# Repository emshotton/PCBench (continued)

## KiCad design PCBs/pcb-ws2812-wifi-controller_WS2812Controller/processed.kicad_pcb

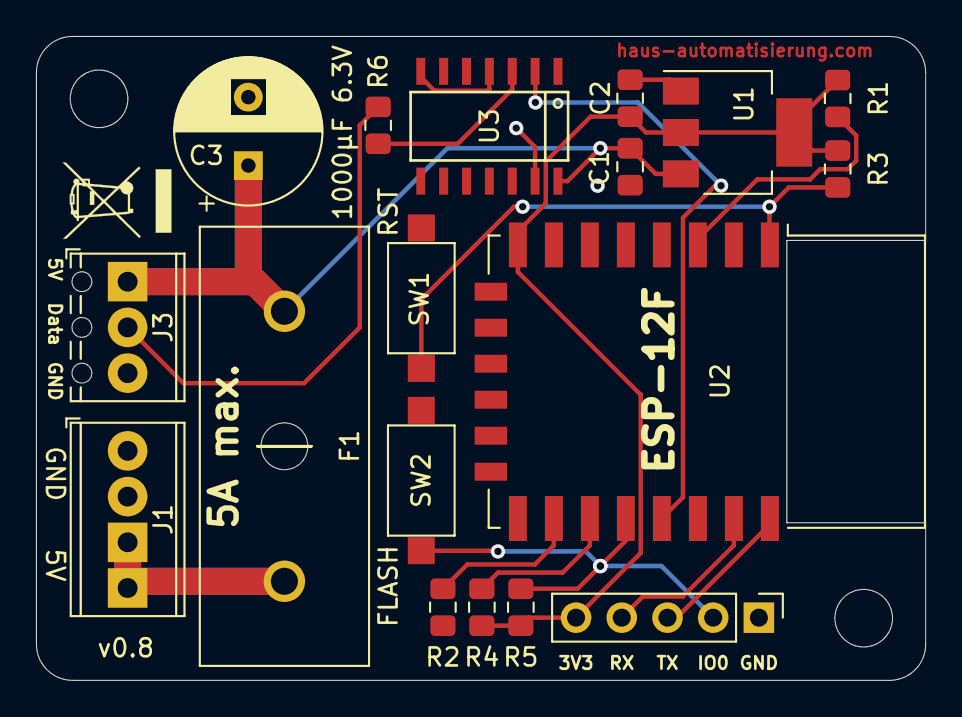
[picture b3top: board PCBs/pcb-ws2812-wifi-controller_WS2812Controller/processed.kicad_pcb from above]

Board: 2 copper layers, 49.4 x 35.8 mm, 18 parts (0 on the bottom side), 14 nets.

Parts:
C1, C2: 100nF; C_0805_2012Metric_Pad1.15x1.40mm_HandSolder
C3: 1000µF; CP_Radial_D8.0mm_P3.80mm
F1: Fuse; Fuse-PTF75_Stelvio
J1: Conn_01x04_Male; TerminalBlock_Phoenix_MPT-0,5-4-2.54_1x04_P2.54mm_Horizontal
J2: Conn_01x05_Male; PinHeader_1x05_P2.54mm_Vertical
J3: Conn_01x03; TerminalBlock_Phoenix_MPT-0,5-3-2.54_1x03_P2.54mm_Horizontal
R1, R2, R3, R4, R5: 10kΩ; R_0805_2012Metric_Pad1.15x1.40mm_HandSolder
R6: 330Ω; R_0805_2012Metric_Pad1.15x1.40mm_HandSolder
SW1: SW_Reset; SW_SPST_CK_RS282G05A3
SW2: SW_GPIO0; SW_SPST_CK_RS282G05A3
U1: AMS1117-3.3; SOT-223-3_TabPin2
U2: ESP-12F; ESP-12E
U3: SN74AHCT125; SN74AHCT125D

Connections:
+3V3: C2.1, J2.5, R1.1, R3.1, R4.1, R5.1, U1.2 (VO), U2.8 (VCC)
+5V: C1.1, C3.1, F1.1, J3.1, U1.3 (VI), U3.14 (VCC)
/EN: R1.2, U2.3 (EN)
/RST: R3.2, SW1.2, U2.1 (~RST)
/SUPPLY: F1.2, J1.3, J1.4
DATA: R6.2, U3.3 (1Y)
GND: C1.2, C2.2, C3.2, J1.1, J1.2, J2.1, J3.3, R2.2, SW1.1, SW2.2, U1.1 (GND), U2.15 (GND), U3.1 (1OE), U3.4 (2OE), U3.7 (GND), U3.10 (3OE), U3.13 (4OE)
GPIO0: J2.2, R5.2, SW2.1, U2.18 (GPIO0)
GPIO4: U2.19 (GPIO4), U3.2 (1A)
unnamed: J3.2, R6.1
unnamed: R2.1, U2.16 (GPIO15)
unnamed: R4.2, U2.17 (GPIO2)
RX: J2.4, U2.21 (GPIO3/RXD)
TX: J2.3, U2.22 (GPIO1/TXD)

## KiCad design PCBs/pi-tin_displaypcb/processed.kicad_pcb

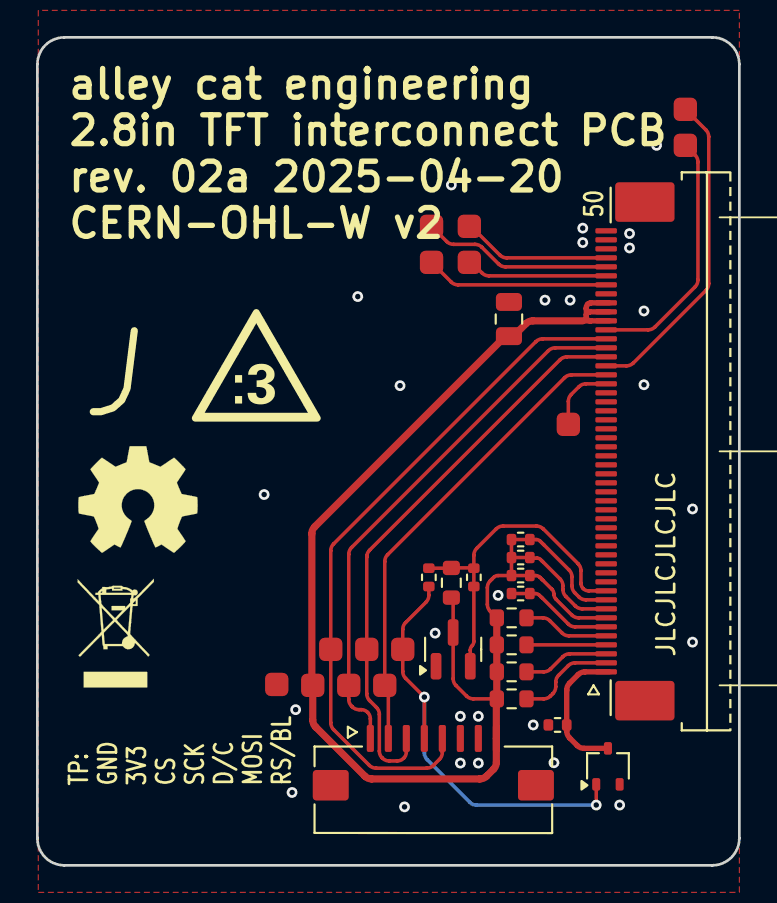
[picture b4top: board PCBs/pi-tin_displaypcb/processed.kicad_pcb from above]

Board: 2 copper layers, 39.0 x 46.0 mm, 32 parts (1 on the bottom side), 25 nets.

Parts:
C101: 10u; C_0805_2012Metric
J102: FPC09-Q1.0-8AH2.0; XYECONN_FPC09-Q1.0-8AH2.0
J103: AFC07-S50ECA-00; Jushuo_AFC07-S50ECA-00
JP101, JP103, JP104, JP105, JP106: SolderJumper_2_Bridged; R_0402_1005Metric_bridged
JP102, JP107: SolderJumper_2_Open; R_0402_1005Metric
N101: Display; TFT_2.8in_ILI9341
Q101: CJ3134KW; SOT-323_SC-70
R101, R102, R103, R105: 10; R_0603_1608Metric
R104: 10k; R_0603_1608Metric
TP101, TP102, TP103, TP104, TP105, TP106, TP107, TP108, TP109, TP110, TP111, TP112, TP113, TP114: TestPoint_Small; TestPoint_Pad_D1.5mm
U101: APX803-31SAG; SOT-23

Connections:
+3.3V: C101.1, J102.8, J103.40, J103.41, J103.42, JP104.1 (A), JP105.1 (A), JP106.1 (A), R101.2, R102.2, R103.2, R104.1, R105.2, TP102.1, U101.3 (VCC)
/D/C: J102.3, J103.36, TP107.1
/IM0: J103.6, JP103.2 (B)
/IM1: J103.7, JP104.2 (B)
/IM2: J103.8, JP105.2 (B)
/IM3: J103.9, JP106.2 (B)
/LEDA1: J103.2, R105.1
/LEDA2: J103.3, R103.1
/LEDA3: J103.4, R102.1
/LEDA4: J103.5, R101.1
/LEDK: J103.1, JP102.2 (B), Q101.3 (D)
/RD: J103.35, TP106.1
/RESET: J103.10, JP101.2 (B), JP107.2 (B), R104.2
/RS/BL: J102.4, JP107.1 (A), Q101.1 (G), TP103.1
/SPI_CS: J102.5, J103.38, TP109.1
/SPI_MISO: J103.33, TP104.1
/SPI_MOSI: J102.2, J103.34, TP105.1
/SPI_SCK: J102.1, J103.37, TP108.1
/TE: J103.39, TP110.1
/XL: J103.46, TP113.1
/XR: J103.44, TP111.1
/YD: J103.45, TP112.1
/YU: J103.47, TP114.1
GND: C101.2, J102.6, J102.7, J102.MP (MountPin), J103.43, J103.48, J103.49, J103.50, J103.MP (MountPin), JP102.1 (A), JP103.1 (A), Q101.2 (S), TP101.1, U101.1 (GND)
unnamed: JP101.1 (A), U101.2 (~RESET)

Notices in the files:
PCBs/pi-tin_displaypcb/processed.kicad_pcb:
CERN-OHL-W v2
Released under the CERN-OHL-W V2 license
